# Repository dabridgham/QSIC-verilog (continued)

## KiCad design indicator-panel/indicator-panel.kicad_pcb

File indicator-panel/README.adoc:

= Indicator Panel

This is an attempt to replicate the functionality of DEC's indicator
panels used on PDP-11s and some other machines.  It was designed in
conjunction with the QSIC project to build a QBUS board to emulate the
old DEC disk drives using more modern storage technology and we wanted
to have blinkenlights to go with.

indicator-panel*::
   KiCad design for the indicator panel boards themselves.  Three
   boards make a full indicator panel.

adapter*:: A small adapter board to convert from the version 1 pinout
   to version 2.

inlay*:: Various inlay designs we've come up with to use with the
   QSIC.

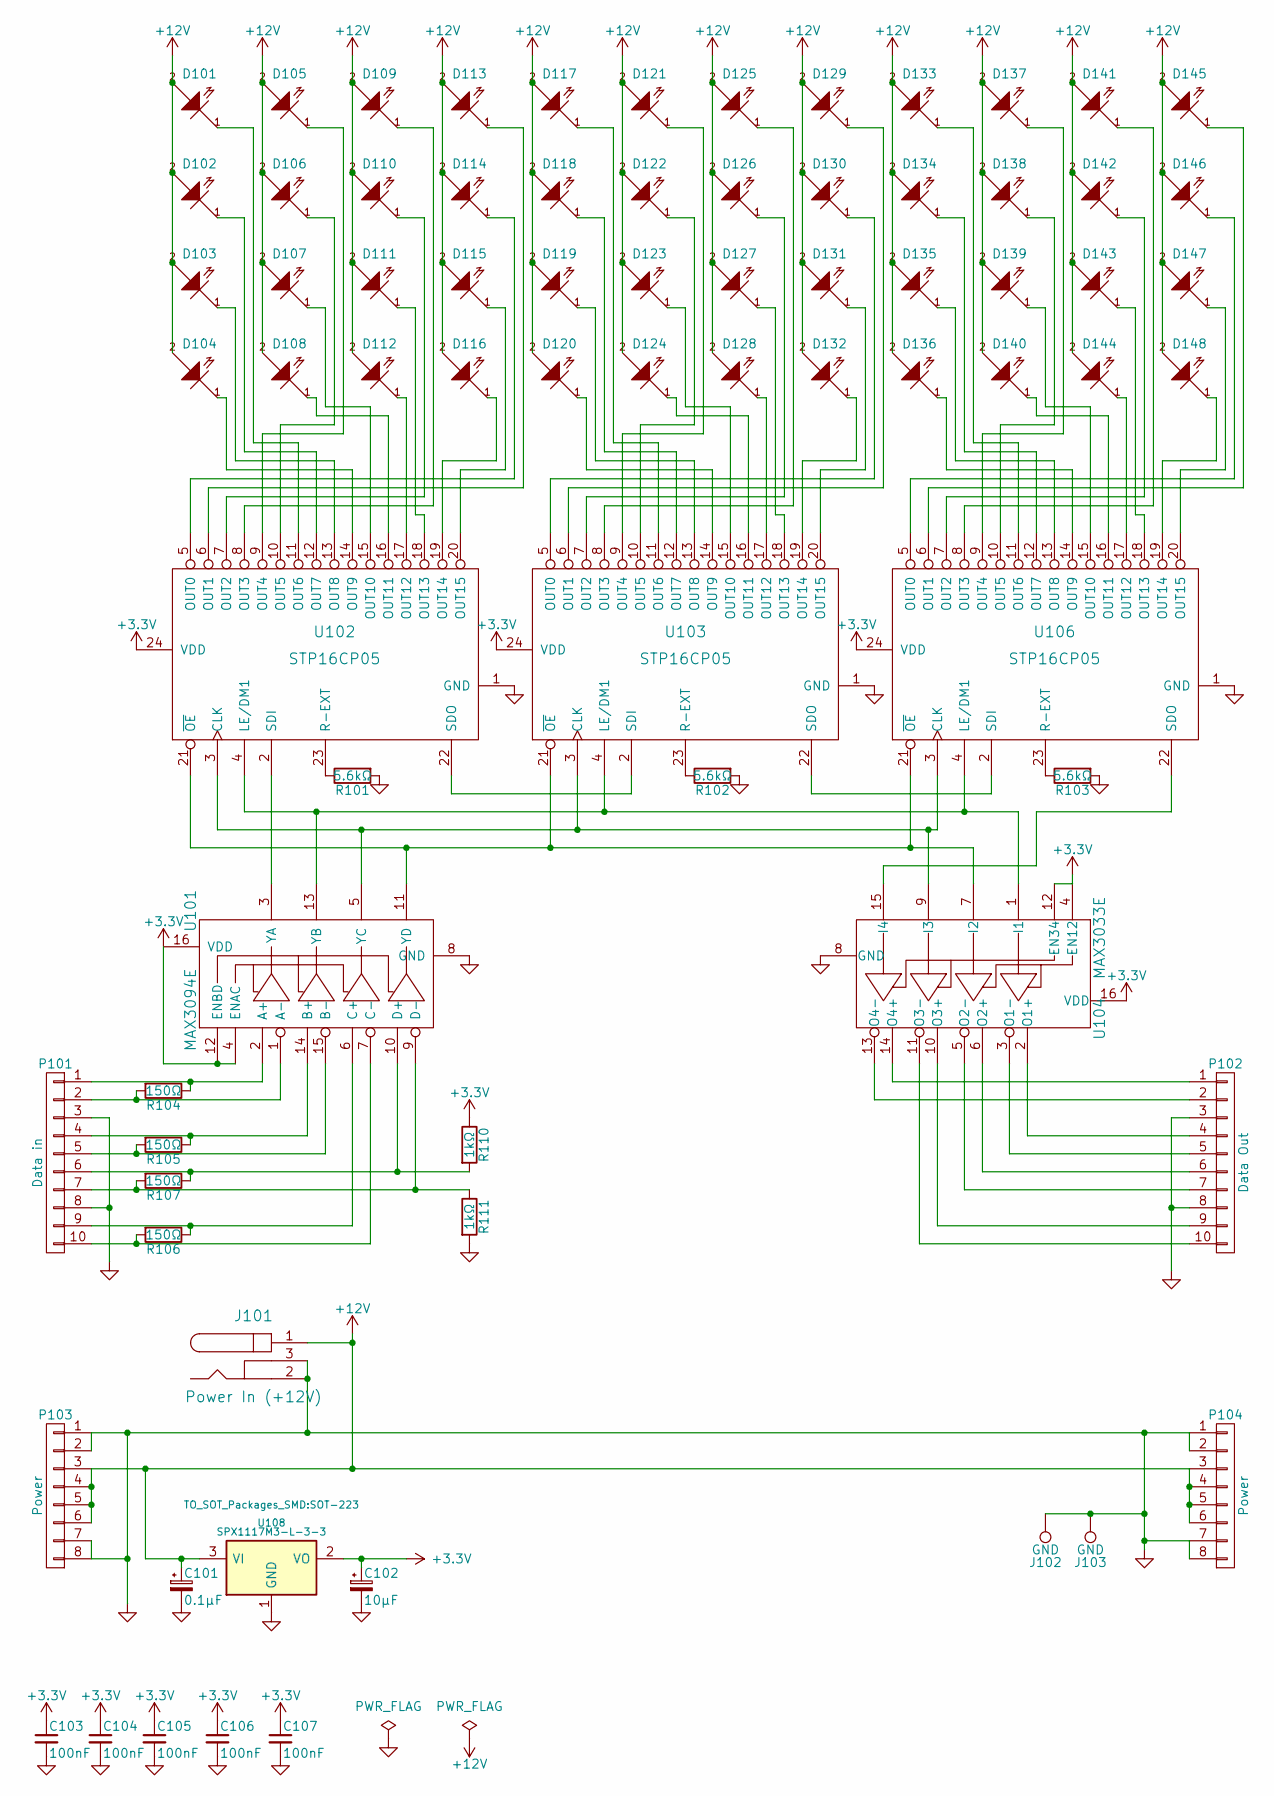
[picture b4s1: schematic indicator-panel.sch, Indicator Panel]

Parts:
C101: 0.1μF; CP_Tantalum_Case-R_EIA-2012-12_Reflow
C102: 10μF; CP_Tantalum_Case-R_EIA-2012-12_Wave
C103, C104, C105, C106, C107: 100nF; C_0805
D101, D102, D103, D104, D105, D106, D107, D108, D109, D110, D111, D112, D113, D114, D115, D116, D117, D118, D119, D120, D121, D122, D123, D124, D125, D126, D127, D128, D129, D130, D131, D132, D133, D134, D135, D136, D137, D138, D139, D140, D141, D142, D143, D144, D145, D146, D147, D148: LED-45; LED-0805
J101: Power In (+12V); PJ-032B
J102, J103: GND; MountingHole_3-5mm
P101: Data in; Pin_Header_Angled_2x05
P102: Data Out; Socket_Strip_Angled_2x05
P103: Power; Pin_Header_Angled_2x04
P104: Power; Socket_Strip_Angled_2x04
R101, R102, R103: 5.6kΩ; R_0805
R104, R105, R106, R107: 150Ω; R_0805
R110, R111: 1kΩ; R_0805
U101: MAX3094E; SOIC-16_3.9x9.9mm_Pitch1.27mm
U102, U103, U106: STP16CP05; SOIC-24_7.5x15.4mm_Pitch1.27mm
U104: MAX3033E; SOIC-16_3.9x9.9mm_Pitch1.27mm
U108: SPX1117M3-L-3-3; SOT-223

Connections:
+3V3: C102.1, C103.1, C104.1, C105.1, C106.1, C107.1, R110.1, U101.4 (ENAC), U101.12 (ENBD), U101.16 (VDD), U102.24 (VDD), U103.24 (VDD), U104.4 (EN12), U104.12 (EN34), U104.16 (VDD), U106.24 (VDD), U108.2 (VO)
+12V: C101.1, D101.2 (A), D102.2 (A), D103.2 (A), D104.2 (A), D105.2 (A), D106.2 (A), D107.2 (A), D108.2 (A), D109.2 (A), D110.2 (A), D111.2 (A), D112.2 (A), D113.2 (A), D114.2 (A), D115.2 (A), D116.2 (A), D117.2 (A), D118.2 (A), D119.2 (A), D120.2 (A), D121.2 (A), D122.2 (A), D123.2 (A), D124.2 (A), D125.2 (A), D126.2 (A), D127.2 (A), D128.2 (A), D129.2 (A), D130.2 (A), D131.2 (A), D132.2 (A), D133.2 (A), D134.2 (A), D135.2 (A), D136.2 (A), D137.2 (A), D138.2 (A), D139.2 (A), D140.2 (A), D141.2 (A), D142.2 (A), D143.2 (A), D144.2 (A), D145.2 (A), D146.2 (A), D147.2 (A), D148.2 (A), J101.1, P103.3, P103.4, P103.5, P103.6, P104.3, P104.4, P104.5, P104.6, U108.3 (VI)
GND: C101.2, C102.2, C103.2, C104.2, C105.2, C106.2, C107.2, J101.2, J101.3, J102.1, J103.1, P101.3, P101.8, P102.3, P102.8, P103.1, P103.2, P103.7, P103.8, P104.1, P104.2, P104.7, P104.8, R101.2, R102.2, R103.2, R111.2, U101.8 (GND), U102.1 (GND), U103.1 (GND), U104.8 (GND), U106.1 (GND), U108.1 (GND)
unnamed: D101.1 (K), U102.11 (OUT6)
unnamed: D102.1 (K), U102.12 (OUT7)
unnamed: D103.1 (K), U102.13 (OUT8)
unnamed: D104.1 (K), U102.14 (OUT9)
unnamed: D105.1 (K), U102.9 (OUT4)
unnamed: D106.1 (K), U102.10 (OUT5)
unnamed: D107.1 (K), U102.15 (OUT10)
unnamed: D108.1 (K), U102.16 (OUT11)
unnamed: D109.1 (K), U102.8 (OUT3)
unnamed: D110.1 (K), U102.7 (OUT2)
unnamed: D111.1 (K), U102.18 (OUT13)
unnamed: D112.1 (K), U102.17 (OUT12)
unnamed: D113.1 (K), U102.6 (OUT1)
unnamed: D114.1 (K), U102.5 (OUT0)
unnamed: D115.1 (K), U102.20 (OUT15)
unnamed: D116.1 (K), U102.19 (OUT14)
unnamed: D117.1 (K), U103.11 (OUT6)
unnamed: D118.1 (K), U103.12 (OUT7)
unnamed: D119.1 (K), U103.13 (OUT8)
unnamed: D120.1 (K), U103.14 (OUT9)
unnamed: D121.1 (K), U103.9 (OUT4)
unnamed: D122.1 (K), U103.10 (OUT5)
unnamed: D123.1 (K), U103.15 (OUT10)
unnamed: D124.1 (K), U103.16 (OUT11)
unnamed: D125.1 (K), U103.8 (OUT3)
unnamed: D126.1 (K), U103.7 (OUT2)
unnamed: D127.1 (K), U103.18 (OUT13)
unnamed: D128.1 (K), U103.17 (OUT12)
unnamed: D129.1 (K), U103.6 (OUT1)
unnamed: D130.1 (K), U103.5 (OUT0)
unnamed: D131.1 (K), U103.20 (OUT15)
unnamed: D132.1 (K), U103.19 (OUT14)
unnamed: D133.1 (K), U106.11 (OUT6)
unnamed: D134.1 (K), U106.12 (OUT7)
unnamed: D135.1 (K), U106.13 (OUT8)
unnamed: D136.1 (K), U106.14 (OUT9)
unnamed: D137.1 (K), U106.9 (OUT4)
unnamed: D138.1 (K), U106.10 (OUT5)
unnamed: D139.1 (K), U106.15 (OUT10)
unnamed: D140.1 (K), U106.16 (OUT11)
unnamed: D141.1 (K), U106.8 (OUT3)
unnamed: D142.1 (K), U106.7 (OUT2)
unnamed: D143.1 (K), U106.18 (OUT13)
unnamed: D144.1 (K), U106.17 (OUT12)
unnamed: D145.1 (K), U106.6 (OUT1)
unnamed: D146.1 (K), U106.5 (OUT0)
unnamed: D147.1 (K), U106.20 (OUT15)
unnamed: D148.1 (K), U106.19 (OUT14)
unnamed: P101.1, R104.1, U101.2 (A+)
unnamed: P101.2, R104.2, U101.1 (A-)
unnamed: P101.4, R105.1, U101.14 (B+)
unnamed: P101.5, R105.2, U101.15 (B-)
unnamed: P101.6, R107.1, R110.2, U101.10 (D+)
unnamed: P101.7, R107.2, R111.1, U101.9 (D-)
unnamed: P101.9, R106.1, U101.6 (C+)
unnamed: P101.10, R106.2, U101.7 (C-)
unnamed: P102.1, U104.14 (O4+)
unnamed: P102.2, U104.13 (O4-)
unnamed: P102.4, U104.2 (O1+)
unnamed: P102.5, U104.3 (O1-)
unnamed: P102.6, U104.6 (O2+)
unnamed: P102.7, U104.5 (O2-)
unnamed: P102.9, U104.10 (O3+)
unnamed: P102.10, U104.11 (O3-)
unnamed: R101.1, U102.23 (R-EXT)
unnamed: R102.1, U103.23 (R-EXT)
unnamed: R103.1, U106.23 (R-EXT)
unnamed: U101.3 (YA), U102.2 (SDI)
unnamed: U101.5 (YC), U102.3 (CLK), U103.3 (CLK), U104.9 (I3), U106.3 (CLK)
unnamed: U101.11 (YD), U102.21 (~OE), U103.21 (~OE), U104.7 (I2), U106.21 (~OE)
unnamed: U101.13 (YB), U102.4 (LE/DM1), U103.4 (LE/DM1), U104.1 (I1), U106.4 (LE/DM1)
unnamed: U102.22 (SDO), U103.2 (SDI)
unnamed: U103.22 (SDO), U106.2 (SDI)
unnamed: U104.15 (I4), U106.22 (SDO)

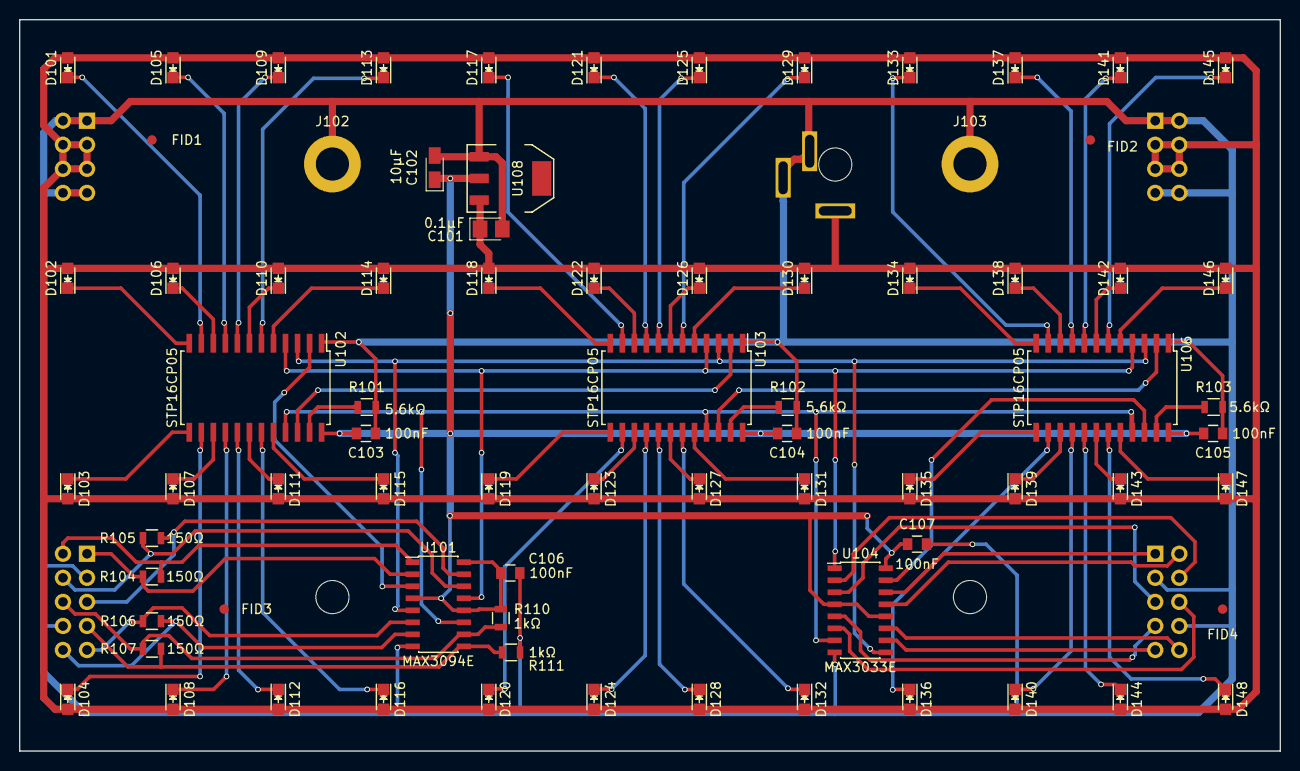
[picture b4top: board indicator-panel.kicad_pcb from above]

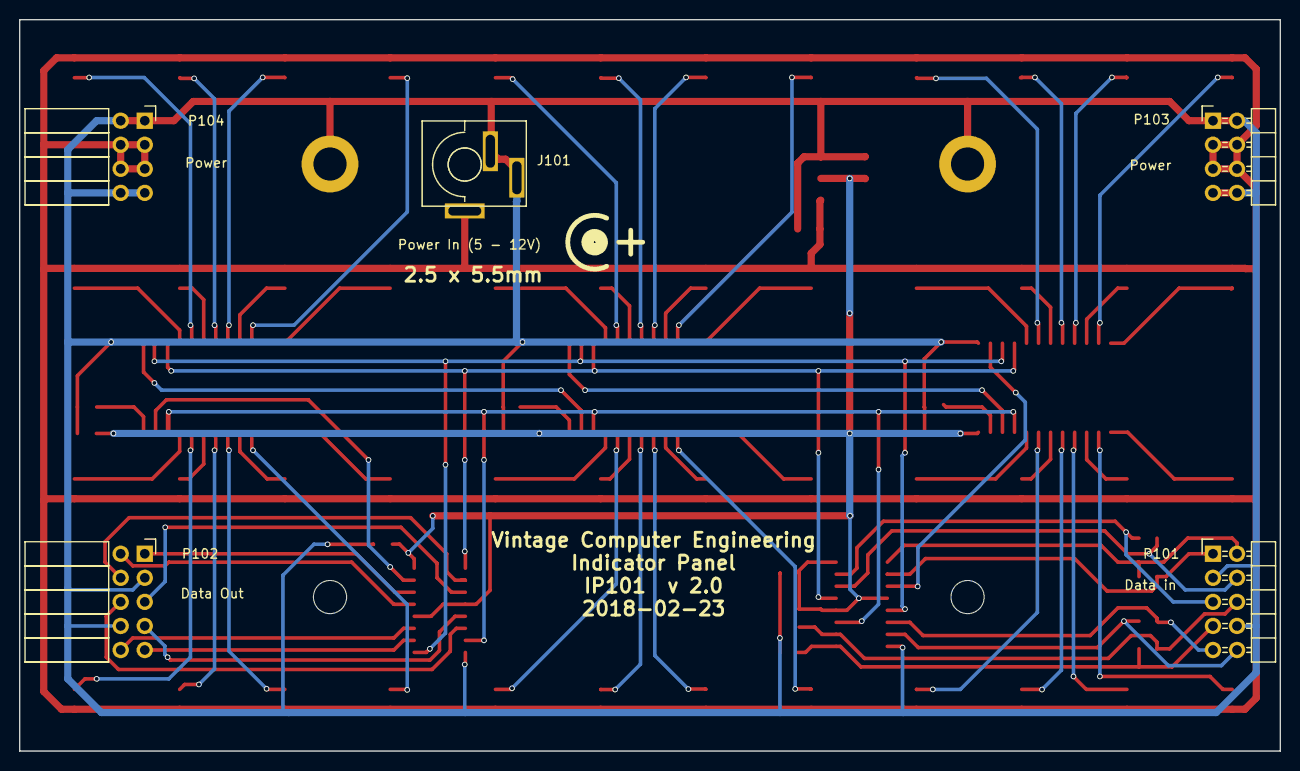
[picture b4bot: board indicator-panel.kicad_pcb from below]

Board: 2 copper layers, 133.1 x 77.2 mm, 81 parts (5 on the bottom side), 77 nets.

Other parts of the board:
FID1, FID2, FID3, FID4: Fiducial; Fiducial_1mm_Dia_2.54mm_Outer_CopperTop

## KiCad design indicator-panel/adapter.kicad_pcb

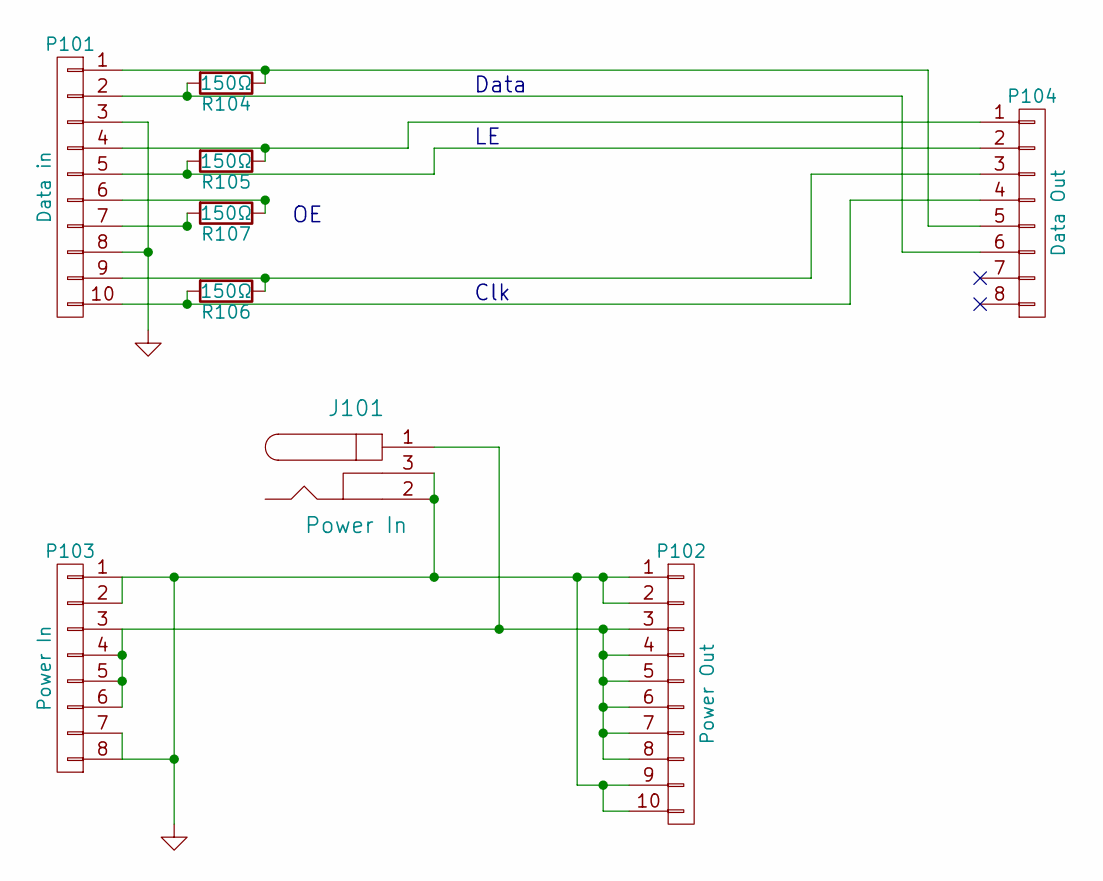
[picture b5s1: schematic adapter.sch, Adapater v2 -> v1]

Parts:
J101: Power In; PJ-032B
P101: Data in; Pin_Header_Straight_2x05
P102: Power Out; Socket_Strip_Straight_2x05
P103: Power In; Pin_Header_Straight_2x04
P104: Data Out; Socket_Strip_Straight_2x04
R104, R105, R106, R107: 150Ω; R_0805

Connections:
GND: J101.2, J101.3, P101.3, P101.8, P102.1, P102.2, P102.9, P102.10, P103.1, P103.2, P103.7, P103.8
unnamed: J101.1, P102.3, P102.4, P102.5, P102.6, P102.7, P102.8, P103.3, P103.4, P103.5, P103.6
unnamed: P101.1, P104.5, R104.1
unnamed: P101.2, P104.6, R104.2
unnamed: P101.4, P104.1, R105.1
unnamed: P101.5, P104.2, R105.2
unnamed: P101.6, R107.1
unnamed: P101.7, R107.2
unnamed: P101.9, P104.3, R106.1
unnamed: P101.10, P104.4, R106.2

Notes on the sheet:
Data
Clk

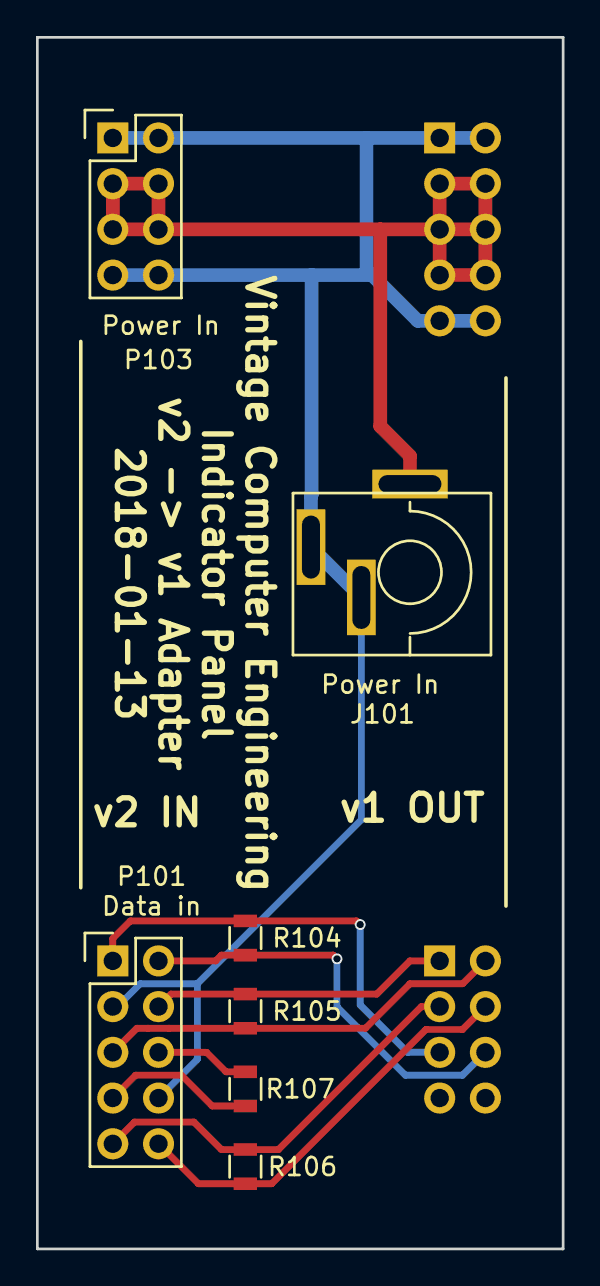
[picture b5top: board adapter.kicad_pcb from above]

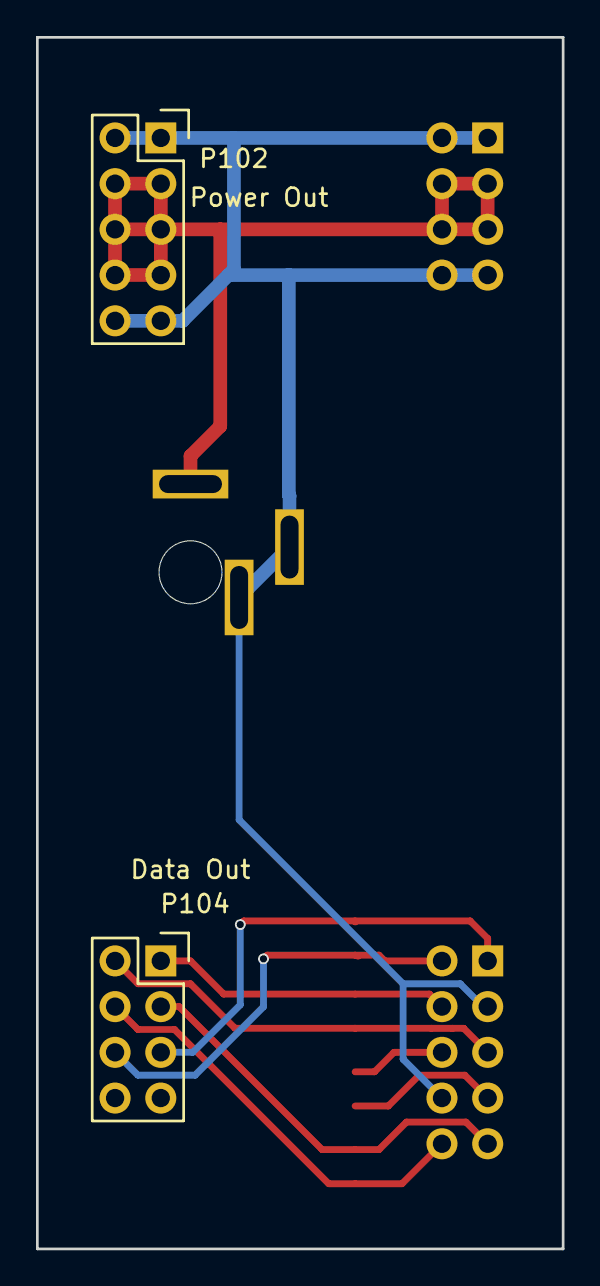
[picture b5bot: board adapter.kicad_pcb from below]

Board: 2 copper layers, 29.2 x 67.3 mm, 9 parts (2 on the bottom side), 10 nets.

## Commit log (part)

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2015-09-22 Initial commit.
2015-09-22 Changed the name of the gtkwave save file.
2015-09-24 Working on conversion to sync internal bus. Not done yet.
2015-10-05 A good start on the DMA mastering logic.
    Started the board layout for discrete bus drivers.
2015-10-08 Added board-prototype.
2015-10-09 Added the bus grant multiplexer.
2015-10-11 Initial checkin of the lights board.
2015-10-12 Renamed lights to indicator-panel.
2015-10-12 Added the simple mechanical drawing for the indicator panel.
2015-10-14 Fix up connectors to carry current.
2015-10-15 Back to a bidirectional DAL bus.
2015-10-15 Full circle, back to using Am2908s and a bidirectional DAL bus. Fixed a few other things along the way, like sorting out the direction and strobe lines and adding level shifting for them.
2015-10-21 In the middle of writing the various modules that enable writing disk controllers.
2015-10-27 Cleaned up schematic and added RK inlay.
2015-10-27 Overlays are really called inlays.
2015-11-09 Added connections to ZTEX FPGA module.
2015-11-11 Updated pcb and rk11 inlay to .44x.88 spacing.
2016-01-10 Fixed bug with gnd on C1. Should be C2 and moved RSYNC down to C14.
2016-01-14 Added barrel connector.
2016-01-24 Moved RSYNC from C14 to B12 so it can be used as a clock.
2016-02-11 Wirewrap board is now split off, this is the PC prototype.
2016-02-14 Split schematic into multiple sheets.
2016-02-17 To the point where qsic-pmo.v works as a simple device register.
2016-02-23 Changed to version 2.0 with the blanking signal and using a 4-unit rs485 receiver and transmitter.
2016-03-08 Got the code to the point where simple DMA transfers and interrupts appear to be working.
2016-03-09 Got Noel's RK exerciser working. WC is negative of the count.
2016-03-20 Fixed the RK code to handle a word-count of 0 to mean 65,536. Our test program doesn't test this case yet but the code before was almost certainly wrong.
2016-04-02 This matches the old indicator panels, the first batch before I changed them all around.
2017-01-15 Added SD card. Not yet wired to FPGA.
2017-01-19 Added a description of the directories
2017-01-29 Added timescale to keep iverilog happy.
2017-01-29 Added in indicator panel connections
2017-01-29 Moved the ramdisk lookup to outside of the always block to keep iverilog happier.
2017-01-29 Modifications to wire up indicator panel
2017-01-29 Changes for the new iverilog and added test.sd
2017-01-29 Monitor QBUS signals plus a little bit of QSIC status
2017-01-29 Updated current limiting resistor to 3.3k
2017-01-29 Changed to comparator for bus receivers and rearranged schematic to multiple pages
2017-01-29 Changed over to only DS8641 bus transceivers and the smaller package level-converters.
2017-02-02 Not nearly done, just putting the code into git
2017-03-16 Committing the last version of the state-machine version before starting down the micro-coding path.
2017-03-20 Changed the SD card driver to be microcoded. It's working in the simulator through card initialization.
2017-03-30 Moved two SD card signals (CS/CD and SD_DO) to ribbon cable wires that are less noisy.
2017-04-01 Added the timescale directive
2017-04-01 Working through SD card initialization on actual hardware.
2017-04-01 Experimenting with trying to make the RAM Disk be block RAM
2017-04-02 ignore indocator-panel/output
2017-04-16 switched over to asciidoc
2017-04-16 works with asciidoctor locally but not on Github
2017-04-16 Apparently Github's asciidoctor doesn't like leading comments.
2017-04-20 Added some voltage regulators.
2017-04-25 Finally put this under git
2017-04-27 Removed the circuits with the flops on the output instead of AND gates and added the section talking about why it's not needed with FPGAs.
2017-04-27 Added the schematics to git.
2017-11-12 The u-assembler now takes its command descrition from a file
2017-11-12 Cleaned up wire lengths
2017-11-20 Added the papers directory
2017-11-23 Fix for correct spacing
2017-11-23 Line up connectors
2017-11-25 Move micro assembler definition for the SD card to this directory and modify to have the new 'sync' bit
2017-11-25 Updated to use correct spacing dimensions
2017-11-26 Moved mounting holes to give a better attach point in the light shield
2017-11-26 Swapped DAL and Latched Address. Re-worked the SD Card display to closer match what I'm doing in debugging the SD Card code.
2017-12-04 Relocated coaxial power connector and increased pad size on its footprint.
2017-12-11 able to write a single block to the SD card
2017-12-11 Build pdf files from the inlay*.svg files.
2017-12-18 Added one more Vivado dropping
2017-12-20 Added commands to make a poster
2017-12-20 Parameterize the GrayCounter
2017-12-20 Add read/write FIFOs between the SD card and the RK11 controller.
2017-12-20 Removed clk input since it's not used.
2017-12-20 Include strobes to read and write data from/to the data FIFOs.
2017-12-20 Working up through writing a static block to the SD card. Writing through the RK11 controller is not yet working.
2017-12-20 Ignore .ps and .bit files.
2017-12-23 I/O devices only check the low 13 bits of the address
2017-12-23 Added rde and wde to control the FIFO
2017-12-23 Reading and writing the SD card now work from the host processor
2017-12-26 A bunch of little things to help with debugging. Also dropped the full-speed to 10MHz to see if speed was causing some of the problems.
2017-12-26 Turn the clock up to full-speed once initialization is done. Added extra delay after CSEL released to give time for Card Detect to settle when running at full speed. Removed the check on the Data Res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
2017-12-26 Rearranged the QBUS indicator to match version two of the design. Added a LAMPTEST version to check out all the lights on indicator panels.
2018-01-14 Updated the pinout to the indicator panel data port to match what I actually built.
2018-01-14 Changed current limiting resistor to 8.2k
2018-01-18 It's QSIC not QBUS
2018-01-18 Moved two of the SD card lines to, hopefully, quieter locations
2018-01-18 Turns SD card speed down to 2.5MHz to gain reliability on the PMo
2018-01-26 Works except that the second to the last word in a block is duplicated in the last word.
2018-01-26 Wired in a Block RAM RAMdisk for testing.
2018-01-30 rkv11 no longer depends on the disk-uc or qreg
2018-01-30 Switched over to the Xilinx FIFOs. Fixed up the indicator panel timing.
2018-01-30 Re-wrote the state machine and implemented partial-block reads and writes. It boots and runs v6 Unix now.
2018-01-30 Restored the overlapped DMA and device write which works right now that I've switched to the Xilinx FIFOs.
2018-02-01 Got the RAM disk using Block RAM working.
2018-02-01 Added the rp11-d-2 poster
2018-02-01 Touch up some dates.
2018-02-26 Finalized v2 signal layout and submitted first batch for production.
2018-02-26 Have two signals from the SD controller, device ready and command ready.
2018-03-03 Get rid of some unused signals.
2018-03-03 Instead of displaying the current value of WC which is going to be very dynamic and then spend most of the time sitting at 0, save the value when a read or write operation starts and display that val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
2018-03-03 Added the Storage Device multiplexer so we can have both the SD card and a RAM disk at the same time. Added a start at a load table as part of this.
2018-03-10 Cleaned up indicator panel
2018-03-10 If init fails, loop back and try again.
2018-03-10 Removed some debugging code.
2018-03-10 A commutator to support multiple indicator panels
2018-03-25 Catch NXM signal correctly on disk reads and implement NXM for disk writes
2018-03-25 Added FIFO reset signal from RK0
2018-03-28 Added rk11-f poster
2018-03-28 Changed the tantalum capacitor footprint to more clearly show the positive end. Added some text around the power connector on the back.
2018-04-05 Fix latch to only fire on the last panel.
2018-04-26 Put the number of cylinders in the load table and fix up the RKV12 to generate the appropriate error if it runs off the end of the disk.
2018-04-26 formatting changes
2018-04-26 Fixed up the simulation a bit to have a closer look at how the bus timing was working.
2018-11-05 Updated to KiCad v5
2018-11-07 Updated to KiCad 5
2018-11-19 Added the Users Manual
2018-11-19 Rewrote the section on the Extended Address Register to be right for 18 or 22 bit addressing on either the QBUS or Unibus and with or without the ENABLE+.
2018-11-21 Print two digit bit numbers on the register diagrams. Put little tick marks between the bits in the register diagrams. Changed the function table formatting in the RK11.
2018-11-22 Make field names in the register diagram be \scriptsize
2018-11-22 Removed \scriptsize from bittable entries since it's now the default
2018-11-22 Import Noel's rewrite.
2018-11-24 Added Noel as an author
2018-11-24 Changed the sectioning a bit and expanded on the issues of 18 and 22-bit addressing.
2018-11-26 Fixed up use of quotes
2018-12-25 Fixed up indicator panel signals to match inlay. Added SCP, slid GO over one spot, removed SKE, and added NXT.
2018-12-25 Small tweaks to title page.
2018-12-25 Adjusted fonts and sizes and spacing of inlays.
2019-01-07 I need to save KiCAD's rescue files as well.
2019-01-07 Note that the indicator panel has moved to its own project.
2019-01-11 Update library references and add rescue file.
2019-01-11 Add rescue file.
2019-01-12 Small fixes as suggested by Verilator.
2019-01-12 Add rescue and cache files
2019-07-06 Changed the format strings to track some changes I made in the micro-assembler
2019-07-06 More little changes from using verilator
2019-07-06 Rearrange for the micro-coded KV10
2019-07-06 Added board-qsic
2019-07-06 Fixed typos
2019-08-27 Added ramdisk-sdram.v and updated path for Vivado 2019.1
2019-08-27 Some ideas now that I've learned about AXI.
2019-08-27 Added ramdisk_sdram and connections to the SDRAM.
2019-10-01 Reworked board from template. Changed schematic to let me use the bus drivers and level converters more efficiently so to get all the signals.
2019-10-12 Design of prototype is done. Needs checking before sending out.
2019-10-12 A few fixups from ERC. Ground CS# on the memory chip.
2019-10-12 Fixed up TDAL[0..21] and RDAL[0.21] buses now that I got it working.
2019-10-12 Updated the date on all the pages.
2020-01-27 Got the RAMDISK working. Had to add a full clock cycle delay when reading the write FIFO since the data seems to be lagging by one clock cycle. Doesn't make sense and will be redone when I change the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
2020-01-27 Added fiducials
2020-01-27 Added 1% to the Vref voltage divider.
2020-01-27 Changes from Emanuel's comments.
2020-01-29 Like writing, reading needs to wait for the read command to go away before it finishes otherwise it might finish too quickly and the disk controller won't ever notice it even started.
2020-01-29 Go back to having an SD disk for RK0 and a RAMdisk for RK1.
2020-01-31 Correct QSIC expansion and other little fixups.
2020-01-31 Update to KiCad v5
2020-01-31 Changed some capacitors from 100nF to 10uF
2020-02-09 Added first cut at configuration documentation.
2020-02-11 Lots of little fixups to the configuration text.
2020-02-24 Minor wording change
2020-02-24 Changed files to Unix format rather than DOS.
2020-02-24 Added some non-breaking spaces between values and units.
2020-04-27 Reordered some of the bit definitions. Need to standardize that throughout the manual. I see that DEC wasn't consistent either.
2020-05-27 Shorten chapter name for page header.
2023-08-10 Just updating now that I'm back to working on the QSIC. Still in the midst of all the big changes for the RP11.
2024-01-06 It's not getting pushed to github for some reason
2024-01-06 Another small change.
2024-01-06 Adding some links
2024-01-06 gotta spell USIC correctly
2024-01-06 These are all old changes in directories that are now historical.
2024-01-06 Still working on getting the big rewrite together. Now that the hardware has been moved to their own projects, committing these to move everything back to the master/main branch.
